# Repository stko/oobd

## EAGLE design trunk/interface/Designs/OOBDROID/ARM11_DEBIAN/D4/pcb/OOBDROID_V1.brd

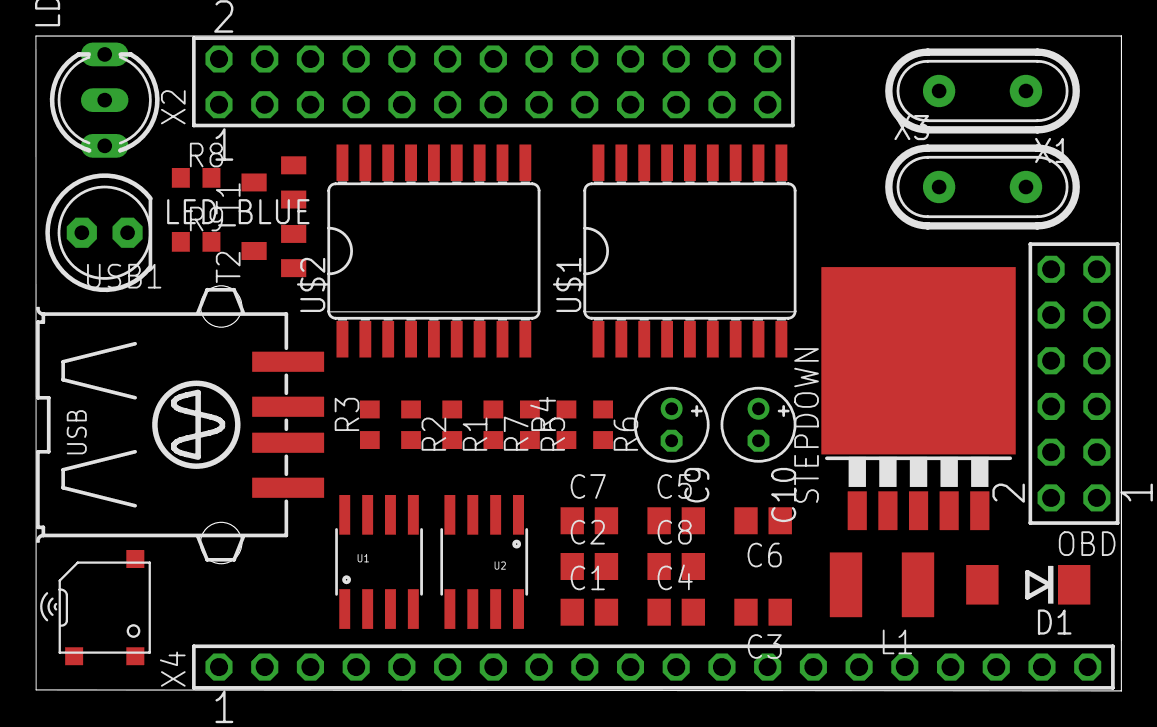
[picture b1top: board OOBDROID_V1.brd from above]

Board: 2 copper layers, 60.3 x 36.4 mm, 37 parts (0 on the bottom side), 40 nets, no tracks yet.

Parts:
C1, C2, C5, C6: 100nF; C0805
C3, C4, C7, C8: 22pF; C0805
C9: 220µF; E1,8-4
C10: 680µF; E1,8-4
D1: 1N5824; DO214AA
L1: 33µH; L4532P
LD2: DUOLED-C-5MM
LED_BLUE: LED5MM
OBD: OOBD-CON; SSW-106-02-S-D
R1, R3: 120R; R0603
R2, R5: 10k; R0603
R4, R8, R9: 4k7; R0603
R6, R7: 82R; R0603
SPK1: SMT-0540-S-R
STEPDOWN: LM2596S; TO263-5
T1: BC847; SOT23
T2: BC817; SOT23
U1, U2: MCP2551; SO08
U$1, U$2: MCP2515SO; SO18L
USB1: USB-A003
X1, X3: 16MHz; HC49
X2: ODROID P1; SSW-113-02-S-D
X4: ODROID-P5; SSW-120-02-S-S

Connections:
GND: C1.2, C2.2, C3.1, C4.1, C5.2, C6.2, C7.1, C8.1, C9.-, C10.-, D1.A, LD2.C, OBD.4, STEPDOWN.3, STEPDOWN.5, T1.2, T2.2, U1.2, U1.8, U2.2, U2.8, U$1.9, U$2.9
unnamed: OBD.5, R1.1, U1.7
unnamed: D1.C, L1.1, STEPDOWN.2
unnamed: C8.2, U$2.7, X3.2
unnamed: C9.+, L1.2, STEPDOWN.4
unnamed: C7.2, U$2.8, X3.1
unnamed: R5.2, U$2.17
unnamed: U2.4, U$2.2
unnamed: U2.1, U$2.1
unnamed: OBD.3, R3.2, U2.6
unnamed: OBD.1, R3.1, U2.7
unnamed: C4.2, U$1.7, X1.2
unnamed: C3.2, U$1.8, X1.1
unnamed: R2.2, U$1.17
unnamed: U1.4, U$1.2
unnamed: U1.1, U$1.1
unnamed: OBD.7, R1.2, U1.6
unnamed: LED_BLUE.K, R9.1
unnamed: U$1.16, X2.26
unnamed: SPK1.+, T1.3
unnamed: R4.2, T1.1
unnamed: LD2.AR, R6.2
unnamed: LD2.AX, R7.1
unnamed: R7.2, X2.15
unnamed: R6.1, X2.13
unnamed: USB1.1, X4.1
unnamed: USB1.4, X4.2
unnamed: USB1.2, X4.3
unnamed: USB1.3, X4.4
unnamed: R4.1, X2.11
unnamed: U$1.12, X2.22
unnamed: U$2.12, X2.18
unnamed: U$2.16, X2.24
unnamed: R9.2, T2.3
unnamed: R8.1, T2.1
unnamed: R8.2, X2.8
unnamed: U$1.14, U$2.14, X2.19
unnamed: U$1.15, U$2.15, X2.21
unnamed: U$1.13, U$2.13, X2.23
VCC: C1.1, C2.1, C5.1, C6.1, C10.+, LED_BLUE.A, OBD.2, R2.1, R5.1, SPK1.-, STEPDOWN.1, U1.3, U2.3, U$1.18, U$2.18

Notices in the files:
parts and their libraries:
SparkFun: Licensing: CC v3.0 Share-Alike You are welcome to use this library for commercial purposes.
